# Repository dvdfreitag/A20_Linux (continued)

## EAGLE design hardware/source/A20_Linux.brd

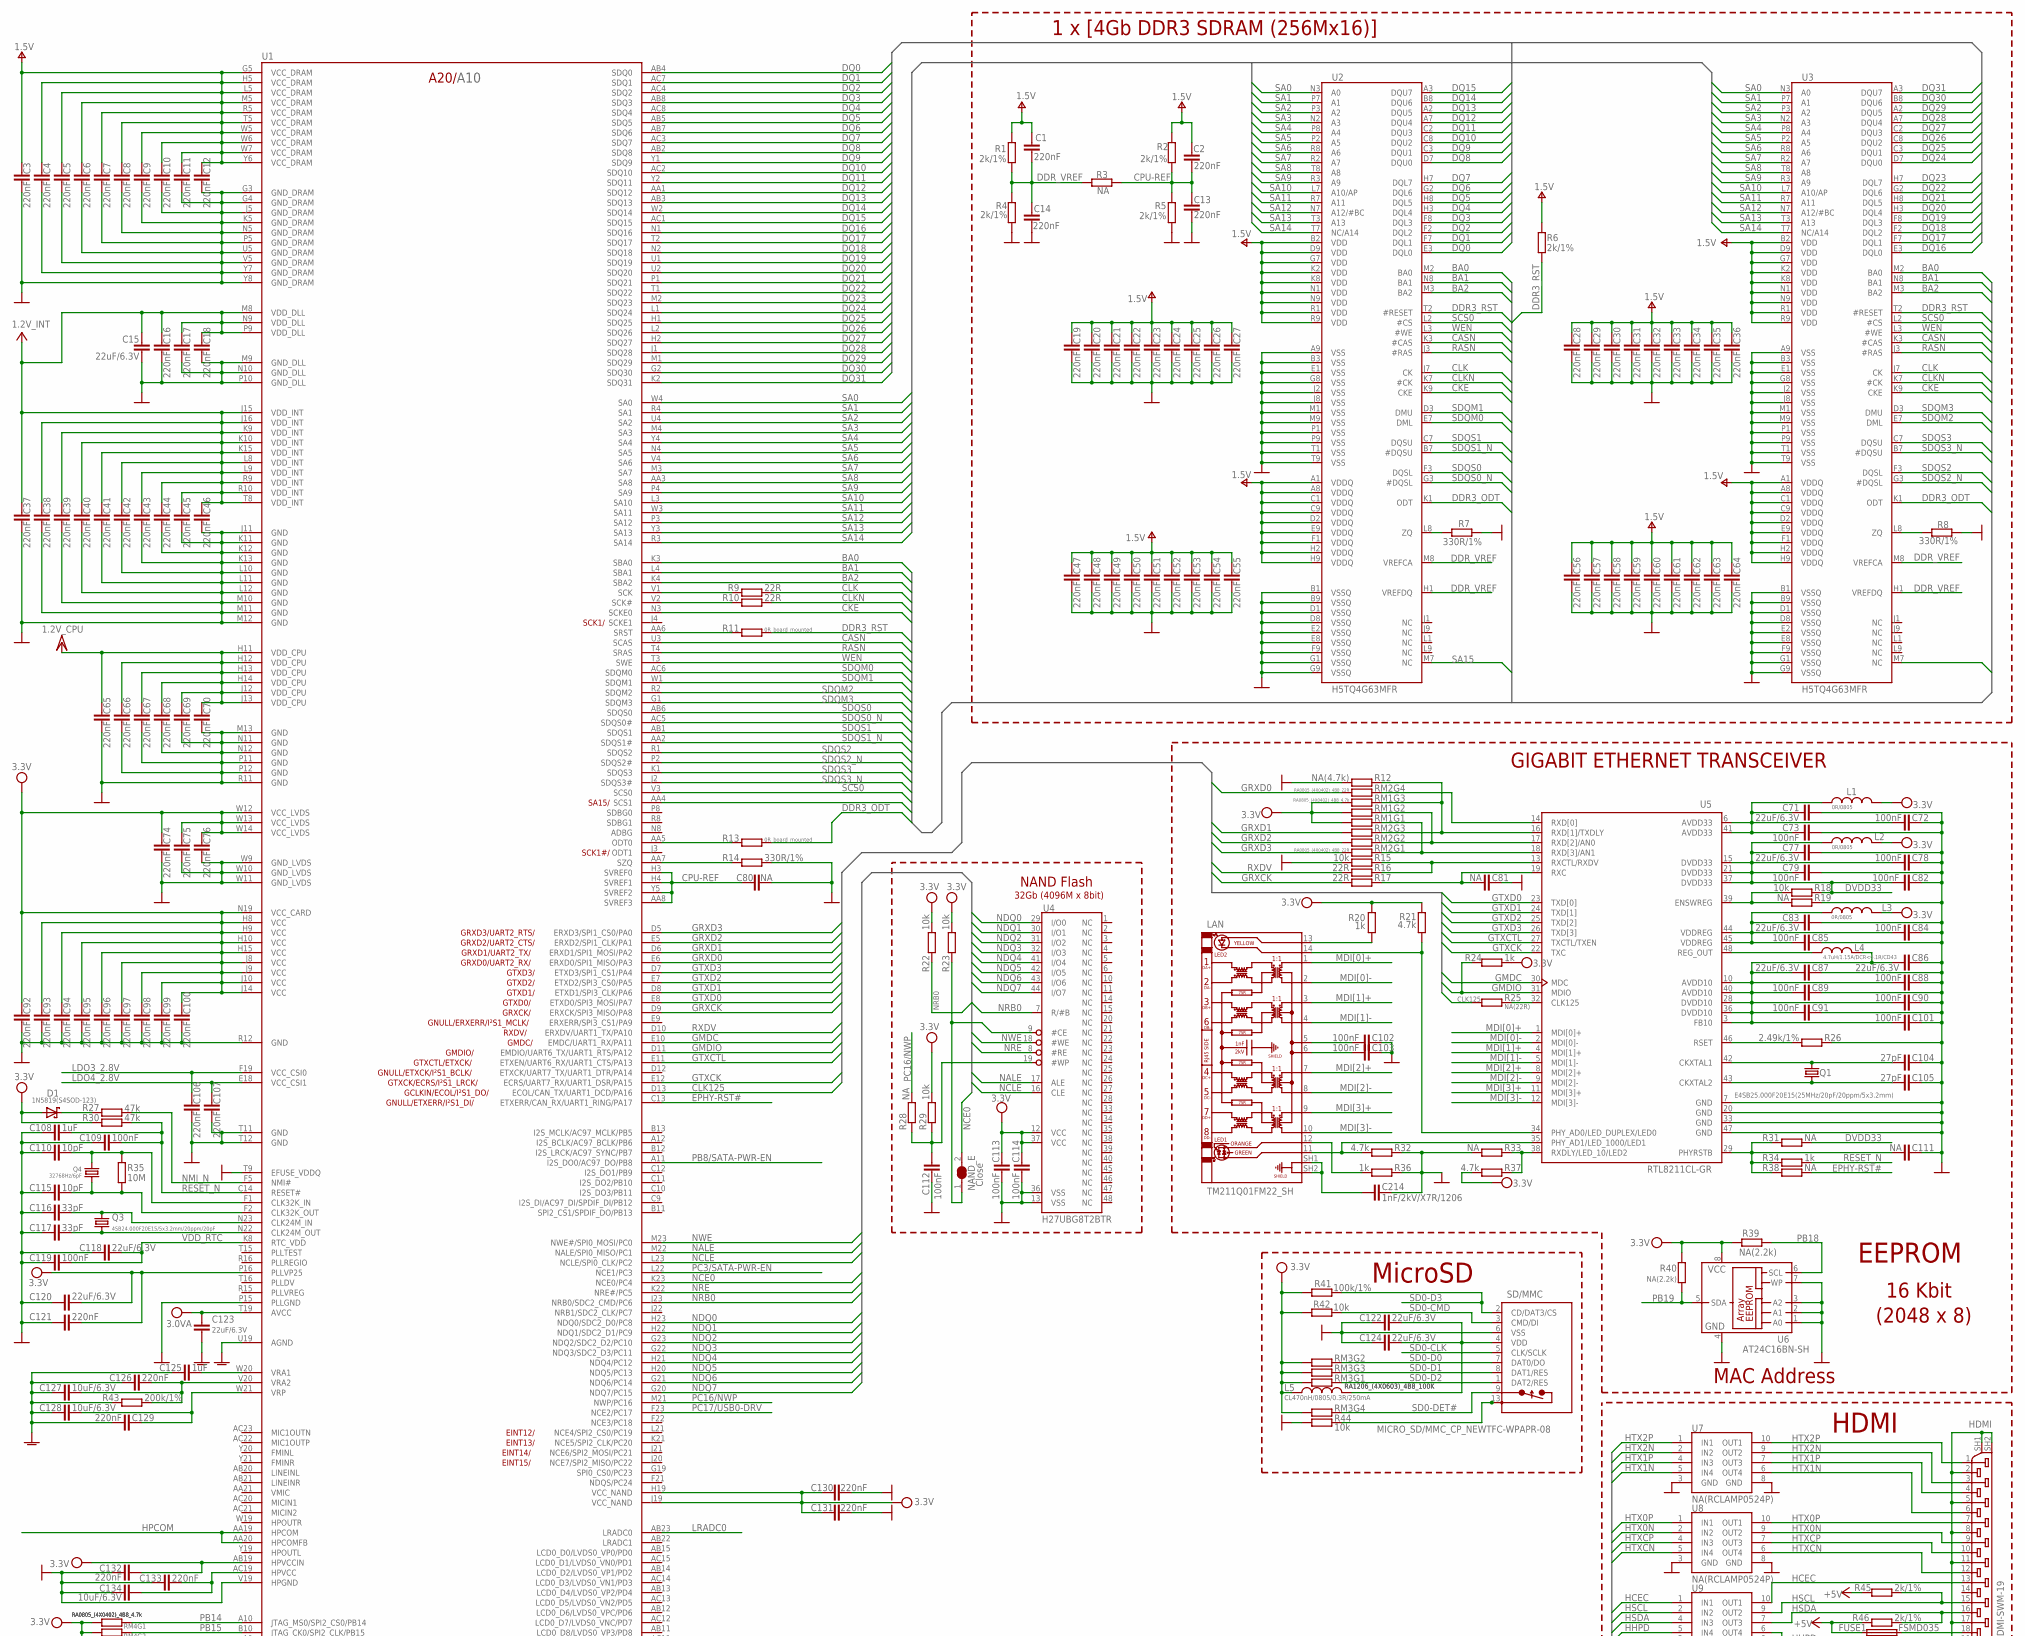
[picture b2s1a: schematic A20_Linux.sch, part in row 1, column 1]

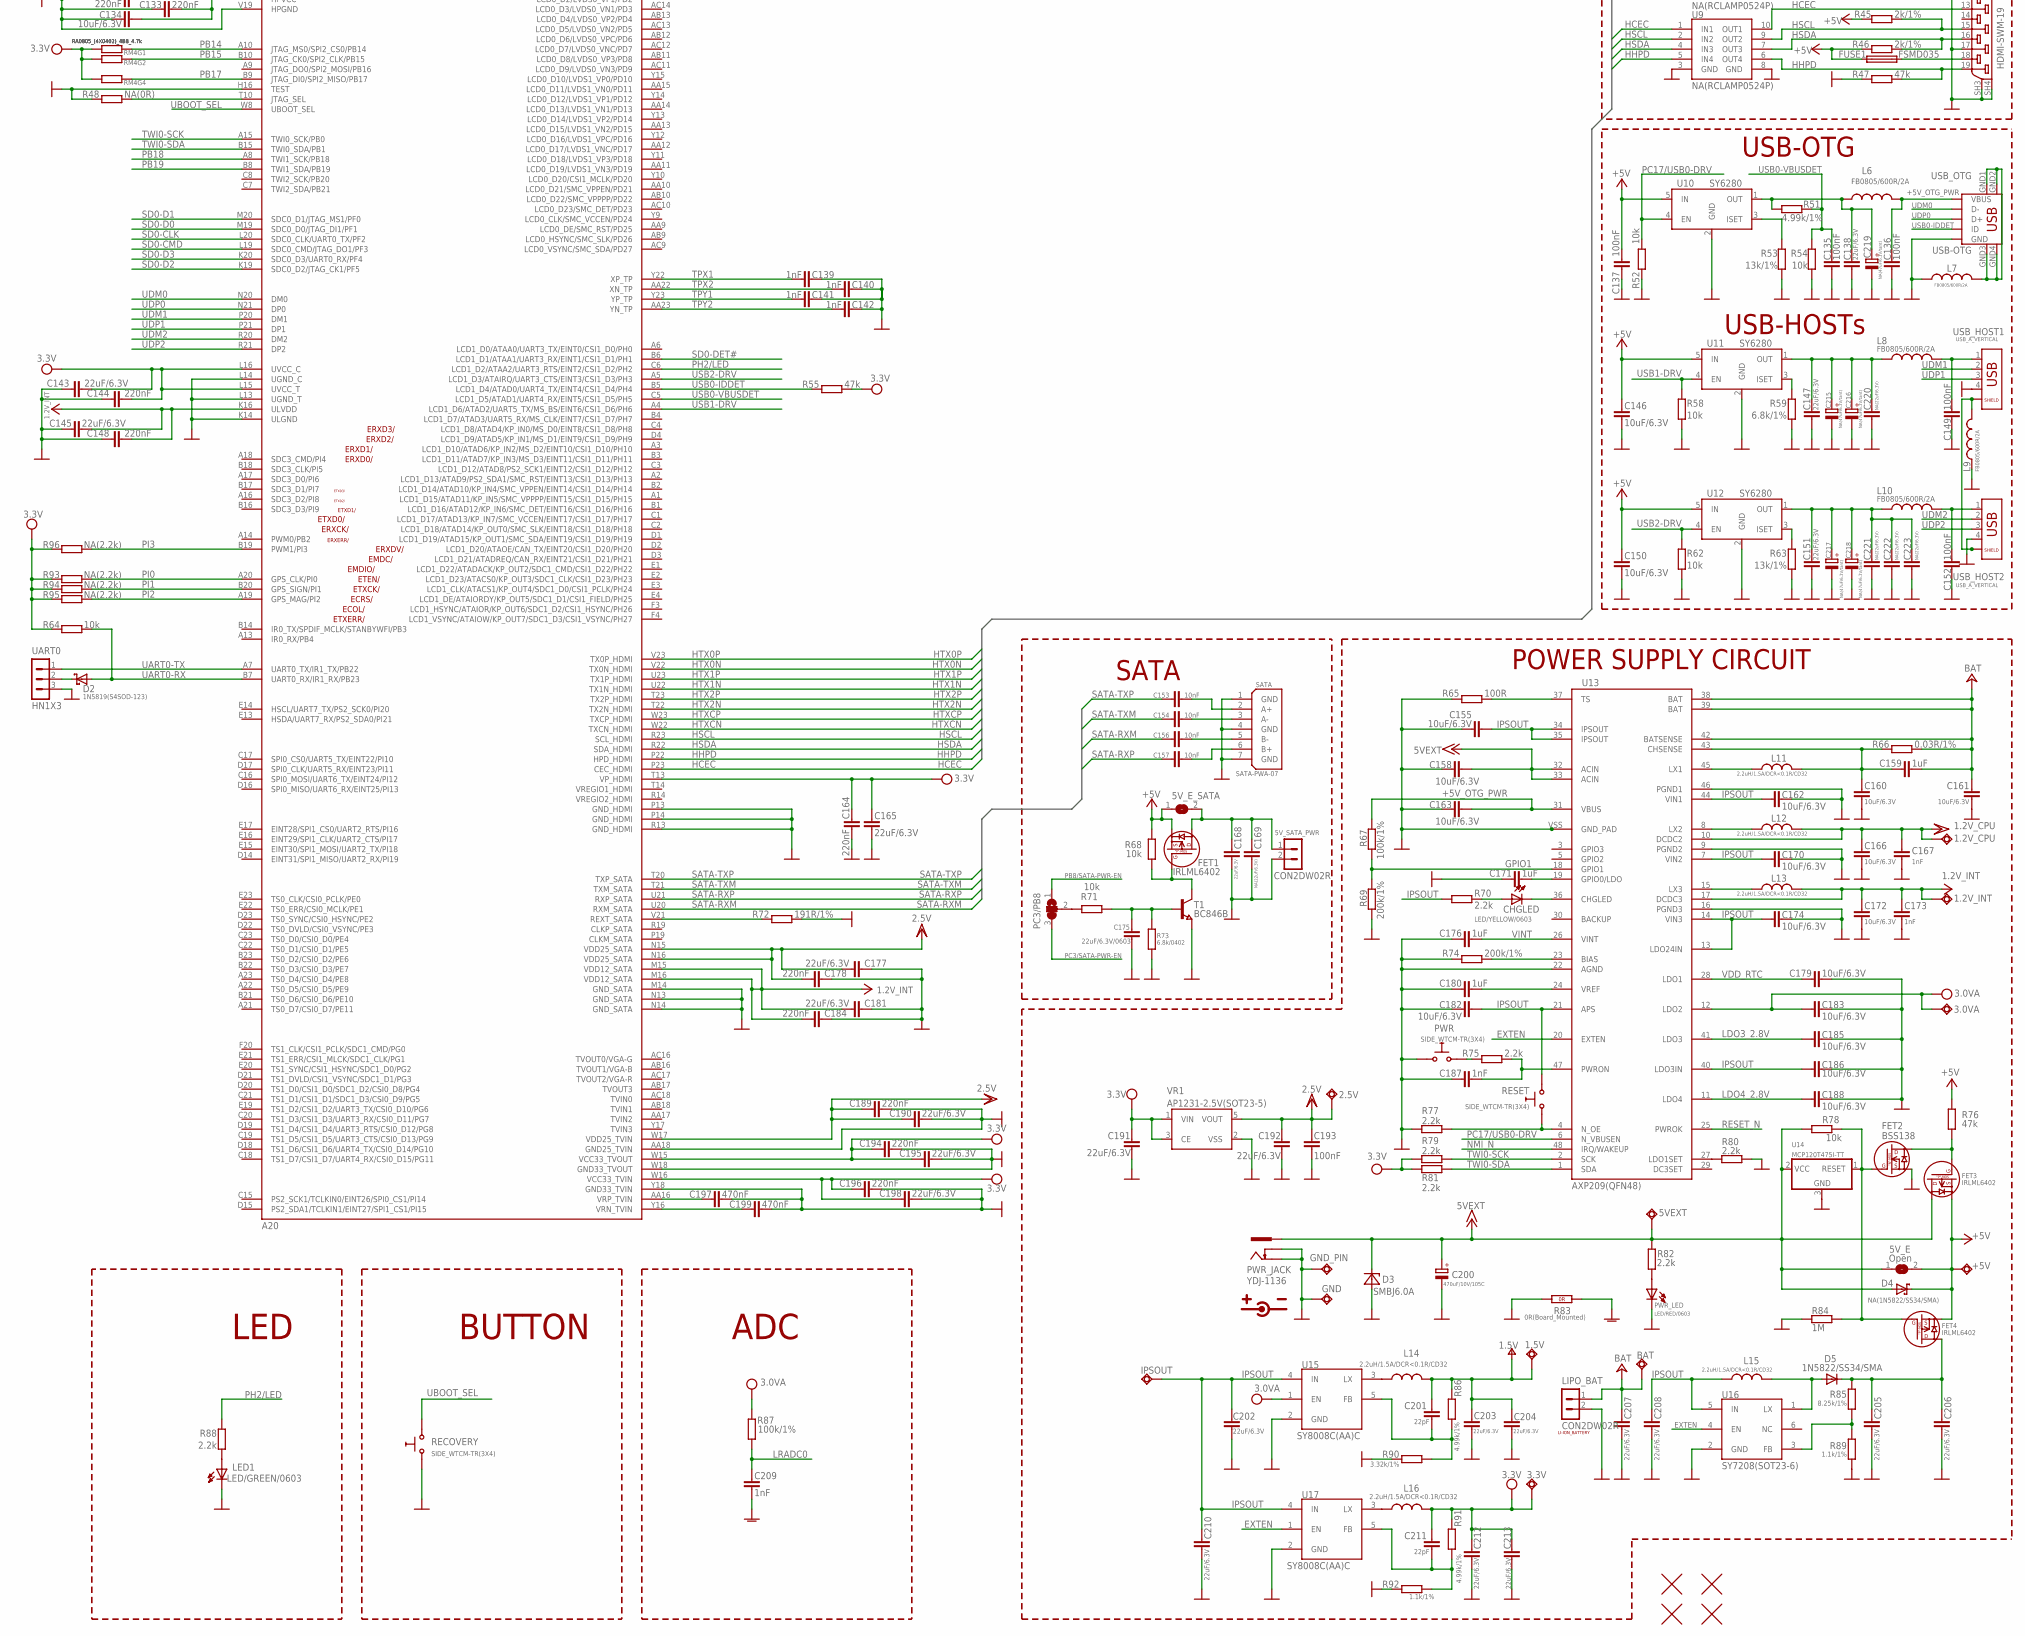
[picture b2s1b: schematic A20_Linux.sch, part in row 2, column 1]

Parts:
1.2V_CPU, 1.2V_INT, 1.5V, 2.5V, 3.0VA, 3.3V, 5VEXT: TESTPADTESTPAD_40-ROUND; TESTPAD_40-ROUND
5V_E: Open; SJ_1_SMALLER
5V_E_SATA: SJSJ_SMALLER; SJ_1_SMALLER
5V_SATA_PWR: CON2DW02R; DW02R
+5V: TESTPADTESTPAD_40-ROUND; TESTPAD_40-ROUND
BAT: TESTPADTESTPAD_40-ROUND; TESTPAD_40-ROUND
C1, C2, C3, C4, C5, C6, C7, C8, C9, C10, C11, C12, C13, C14, C16, C17, C18, C19, C20, C21, C22, C23, C24, C25, C26, C27, C28, C29, C30, C31, C32, C33, C34, C35, C36, C37, C38, C39, C40, C41, C42, C43, C44, C45, C46, C47, C48, C49, C50, C51, C52, C53, C54, C55, C56, C57, C58, C59, C60, C61, C62, C63, C64, C65, C66, C67, C68, C69, C70, C74, C75, C76, C92, C93, C94, C95, C96, C97, C98, C99, C100, C106, C107, C121, C126, C129, C130, C131, C132, C133, C144, C148, C164, C178, C184, C189, C194, C196: 220nF; C0402_TI
C15, C71, C77, C83, C86, C87, C118, C120, C122, C123, C124, C138, C143, C145, C147, C151, C165, C168, C177, C181, C190, C191, C192, C195, C198, C202, C203, C204, C205, C206, C207, C208, C210, C212, C213: 22uF/6.3V; C0603_DWS
C72, C73, C78, C79, C82, C84, C85, C88, C89, C90, C91, C101, C102, C103, C109, C112, C113, C114, C119, C135, C136, C137, C149, C152, C193: 100nF; C0402_TI
C80, C81, C111: NA; C0402_TI
C104, C105: 27pF; C0603_DWS
C108, C125, C159, C171, C176, C180: 1uF; C0603_DWS
C110, C115: 10pF; C0402_TI
C116, C117: 33pF; C0603_DWS
C127, C128, C134, C146, C150, C155, C158, C160, C161, C162, C163, C166, C170, C172, C174, C179, C182, C183, C185, C186, C188: 10uF/6.3V; C0603_DWS
C139, C140, C141, C142, C167, C173, C187, C209: 1nF; C0402_TI
C153, C154, C156, C157: 10nF; C0402_TI
C169, C220, C221, C222, C223: NA(22uF/6.3V); C0603_DWS
C175: 22uF/6.3V/0603; C0402_TI
C197, C199: 470nF; C0603_DWS
C200: 470uF/10V/105C; E2,5-6,3
C201, C211: 22pF; C0603_DWS
C214: 1nF/2kV/X7R/1206; C1206_5MILS_WS_ISO
C215, C216, C217, C218, C219: NA(47uF/6.3V/tant); CT3528_MIL
CHGLED: LED/YELLOW/0603; LED-0603
D1, D2: 1N5819(S4SOD-123); SOD-123
D3: SMBJ6.0A; DO214AA
D4: NA(1N5822/SS34/SMA); MLL-41
D5: 1N5822/SS34/SMA; MELF-MLL41
FET1, FET3, FET4: IRLML6402; SOT23
FET2: BSS138; SOT23
FUSE1: FSMD035; 1206
GND: TESTPADTESTPAD_40-ROUND; TESTPAD_40-ROUND
GND_PIN: TESTPAD3; TEST_PAD40/70/SQUARE
HDMI: HDMI-SWM-19
IPSOUT: TESTPADTESTPAD_40-ROUND; TESTPAD_40-ROUND
L1, L2, L3: 0R/0805; L0805_5MIL_DWS
L4: 4.7uH/1.15A/DCR<0.1R/CD43; CD42(43)
L5: CL470nH/0805/0.3R/250mA; L0805_5MIL_DWS
L6, L7, L8, L9, L10: FB0805/600R/2A; L0805_5MIL_DWS
L11, L12, L13, L14, L15, L16: 2.2uH/1.5A/DCR<0.1R/CD32; CD32
LAN: TM211Q01FM22_SH
LED1: LED/GREEN/0603; LED-0603
LIPO_BAT: CON2DW02R; DW02R
NAND_E: Close; SJ_1_SMALLER_CLOSE_10MILS
PC3/PB8: SJ2W5; SJ_2_SMALL_23_TIED
PWR: SIDE_WTCM-TR(3X4); SW_TAKT3X4
PWR_JACK: YDJ-1136; PWR_JACK_UNI_MILLING
PWR_LED: LED/RED/0603; LED-0603
Q1: E4SB25.000F20E15(25MHz/20pF/20ppm/5x3.2mm); HCX-4S
Q3: 4SB24.000F20E15/5x3.2mm/20ppm/20pF; HCX-4S
Q4: 32768Hz/6pF; MC-306
R1, R2, R4, R5, R6, R45, R46: 2k/1%; R0402_TI
R3, R19, R28, R31, R33, R38: NA; R0402_TI
R7, R8, R14: 330R/1%; R0603_5MIL_DWS
R9, R10, R16, R17: 22R; R0402_TI
R11, R13: 0R_board_mounted; R0402_TI_0R
R12: NA(4.7k); R0402_TI
R15, R18, R22, R23, R29, R42, R44, R52, R54, R58, R62, R64, R68, R71, R78: 10k; R0402_TI
R20, R24, R34, R36: 1k; R0402_TI
R21, R32, R37: 4.7k; R0402_TI
R25: NA(22R); R0402_TI
R26: 2.49k/1%; R0603_5MIL_DWS
R27, R30, R47, R55, R76: 47k; R0402_TI
R35: 10M; R0402_TI
R39, R40, R93, R94, R95, R96: NA(2.2k); R0402_TI
R41, R67, R87: 100k/1%; R0603_5MIL_DWS
R43, R69, R74: 200k/1%; R0603_5MIL_DWS
R48: NA(0R); R0603_5MIL_DWS
R51, R86, R91: 4.99k/1%; R0603_5MIL_DWS
R53, R63: 13k/1%; R0603_5MIL_DWS
R59: 6.8k/1%; R0603_5MIL_DWS
R65: 100R; R0603_5MIL_DWS
R66: 0.03R/1%; R1206_5MIL_WS
R70, R75, R77, R79, R80, R81, R82, R88: 2.2k; R0402_TI
R72: 191R/1%; R0603_5MIL_DWS
R73: 6.8k/0402; R0603_5MIL_DWS
R83: 0R(Board_Mounted); 0603_0R
R84: 1M; R0402_TI
R85: 8.25k/1%; R0603_5MIL_DWS
R89, R92: 1.1k/1%; R0603_5MIL_DWS
R90: 3.32k/1%; R0603_5MIL_DWS
RECOVERY: SIDE_WTCM-TR(3X4); SW_TAKT3X4
RESET: SIDE_WTCM-TR(3X4); SW_TAKT3X4
RM1, RM4: RA0805_(4X0402)_4B8_4.7k; R_MATRIX_4_0402_25X625
RM2: RA0805_(4X0402)_4B8_22R; R_MATRIX_4_0402_25X625
RM3: RA1206_(4X0603)_4B8_100K; R_MATRIX_4
SATA: SATA-PWA-07
SD/MMC: MICRO_SD/MMC_CP_NEWTFC-WPAPR-08; TFC-WPAPR-08
T1: BC846B; SOT23
U1: A20; TFBGA441
U2, U3: H5TQ4G63MFR; FBGA96_SK
U4: H27UBG8T2BTR; TSOP48
U5: RTL8211CL-GR; LQFP48
U6: AT24C16BN-SH; SO-08MN
U7, U8, U9: NA(RCLAMP0524P); SLP2510P8
U10, U11, U12: SY6280; SOT23-5
U13: AXP209(QFN48); QFN48
U14: MCP120T475I-TT; SOT23
U15, U17: SY8008C(AA)C; SOT23-5
U16: SY7208(SOT23-6); SOT23-6
U18, U19, U20, U21: FIDUCIAL; FIDUCIAL-1X3
UART0: HN1X3
USB_HOST1, USB_HOST2: USB_A_VERTICAL; USB_A_VERTICAL_PTH
USB_OTG: USB-OTG; USB_MINI_9PIN
VR1: AP1231-2.5V(SOT23-5); SOT-23-5

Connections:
5VEXT: 5VEXT.1, 5V_E.1, C158.2, C200.+, D3.C, D4.A, FET3.3 (D), PWR_JACK.+, R78.1, R82.1, U13.32 (ACIN), U13.33 (ACIN), U14.2 (VCC)
+5V: 5V_E.2, 5V_E_SATA.1, +5V.1, C137.1, C146.1, C150.1, D4.K (C), FET1.2 (S), FET3.2 (S), FET4.2 (S), FUSE1.1, R45.2, R46.2, R68.1, R76.2, U10.5 (IN), U11.5 (IN), U12.5 (IN)
+5V_OTG_PWR: C136.1, C163.2, L6.1, R67.1, U13.31 (VBUS), USB_OTG.VBUS
+24V: BAT.1, C159.2, C161.1, C207.2, LIPO_BAT.1, R66.2, U13.38 (BAT), U13.39 (BAT), U13.42 (BATSENSE)
AVDD1: C71.2, C72.2, C73.2, L1.2, U5.6 (AVDD33), U5.41 (AVDD33)
AVDD/DVDD(1.05V): C86.2, C87.2, C88.2, C89.2, C90.2, C91.2, C101.2, L4.2, U5.3 (FB10), U5.10 (AVDD10), U5.28 (DVDD10), U5.36 (DVDD10), U5.40 (AVDD10)
BA0: U1.K3 (SBA0), U2.M2 (BA0), U3.M2 (BA0)
BA1: U1.L4 (SBA1), U2.N8 (BA1), U3.N8 (BA1)
BA2: U1.K4 (SBA2), U2.M3 (BA2), U3.M3 (BA2)
CASN: U1.U3 (SCAS), U2.K3 (#CAS), U3.K3 (#CAS)
CKE: U1.N3 (SCKE0), U2.K9 (CKE), U3.K9 (CKE)
CLK: R9.1, U2.J7 (CK), U3.J7 (CK)
CLK125: R25.1, U1.D13 (ECOL/CAN_TX/UART1_DCD/PA16)
CLKN: R10.1, U2.K7 (#CK), U3.K7 (#CK)
CPU-REF: C2.2, C13.2, C80.2, R2.1, R3.2, R5.2, U1.AA8 (SVREF3), U1.H3 (SVREF0), U1.H4 (SVREF1), U1.Y5 (SVREF2)
DDR3_ODT: R13.1, U2.K1 (ODT), U3.K1 (ODT)
DDR3_RST: R6.1, R11.1, U2.T2 (#RESET), U3.T2 (#RESET)
DDR_VREF: C1.2, C14.2, R1.1, R3.1, R4.2, U2.H1 (VREFDQ), U2.M8 (VREFCA), U3.H1 (VREFDQ), U3.M8 (VREFCA)
DQ0: U1.AB4 (SDQ0), U2.E3 (DQL0)
DQ1: U1.AC7 (SDQ1), U2.F7 (DQL1)
DQ2: U1.AC4 (SDQ2), U2.F2 (DQL2)
DQ3: U1.AB8 (SDQ3), U2.F8 (DQL3)
DQ4: U1.AC8 (SDQ4), U2.H3 (DQL4)
DQ5: U1.AB5 (SDQ5), U2.H8 (DQL5)
DQ6: U1.AB7 (SDQ6), U2.G2 (DQL6)
DQ7: U1.AC3 (SDQ7), U2.H7 (DQL7)
DQ8: U1.AB2 (SDQ8), U2.D7 (DQU0)
DQ9: U1.Y1 (SDQ9), U2.C3 (DQU1)
DQ10: U1.AC2 (SDQ10), U2.C8 (DQU2)
DQ11: U1.Y2 (SDQ11), U2.C2 (DQU3)
DQ12: U1.AA1 (SDQ12), U2.A7 (DQU4)
DQ13: U1.AB3 (SDQ13), U2.A2 (DQU5)
DQ14: U1.W2 (SDQ14), U2.B8 (DQU6)
DQ15: U1.AC1 (SDQ15), U2.A3 (DQU7)
DQ16: U1.N1 (SDQ16), U3.E3 (DQL0)
DQ17: U1.T2 (SDQ17), U3.F7 (DQL1)
DQ18: U1.N2 (SDQ18), U3.F2 (DQL2)
DQ19: U1.U1 (SDQ19), U3.F8 (DQL3)
DQ20: U1.U2 (SDQ20), U3.H3 (DQL4)
DQ21: U1.P1 (SDQ21), U3.H8 (DQL5)
DQ22: U1.T1 (SDQ22), U3.G2 (DQL6)
DQ23: U1.M2 (SDQ23), U3.H7 (DQL7)
DQ24: U1.L1 (SDQ24), U3.D7 (DQU0)
DQ25: U1.H1 (SDQ25), U3.C3 (DQU1)
DQ26: U1.L2 (SDQ26), U3.C8 (DQU2)
DQ27: U1.H2 (SDQ27), U3.C2 (DQU3)
DQ28: U1.J1 (SDQ28), U3.A7 (DQU4)
DQ29: U1.M1 (SDQ29), U3.A2 (DQU5)
DQ30: U1.G2 (SDQ30), U3.B8 (DQU6)
DQ31: U1.K2 (SDQ31), U3.A3 (DQU7)
DVDD33: C77.2, C78.2, C79.2, C82.2, L2.2, R18.1, R31.1, U5.15 (DVDD33), U5.21 (DVDD33), U5.37 (DVDD33)
EPHY-RST#: R38.1, U1.C13 (ETXERR/CAN_RX/UART1_RING/PA17)
EXTEN: U13.20 (EXTEN), U16.4 (EN), U17.1 (EN)
GMDC: U1.E10 (EMDC/UART1_RX/PA11), U5.30 (MDC)
GMDIO: R24.1, U1.D11 (EMDIO/UART6_TX/UART1_RTS/PA12), U5.31 (MDIO)
GND: 5V_SATA_PWR.2, C3.1, C4.1, C5.1, C6.1, C7.1, C8.1, C9.1, C10.1, C11.1, C12.1, C13.1, C14.1, C15.1, C16.1, C17.1, C18.1, C19.1, C20.1, C21.1, C22.1, C23.1, C24.1, C25.1, C26.1, C27.1, C28.1, C29.1, C30.1, C31.1, C32.1, C33.1, C34.1, C35.1, C36.1, C37.1, C38.1, C39.1, C40.1, C41.1, C42.1, C43.1, C44.1, C45.1, C46.1, C47.1, C48.1, C49.1, C50.1, C51.1, C52.1, C53.1, C54.1, C55.1, C56.1, C57.1, C58.1, C59.1, C60.1, C61.1, C62.1, C63.1, C64.1, C65.1, C66.1, C67.1, C68.1, C69.1, C70.1, C71.1, C72.1, C73.1, C74.1, C75.1, C76.1, C77.1, C78.1, C79.1, C80.1, C81.2, C82.1, C83.1, C84.1, C85.1, C86.1, C87.1, C88.1, C89.1, C90.1, C91.1, C92.1, C93.1, C94.1, C95.1, C96.1, C97.1, C98.1, C99.1, C100.1, C101.1, C102.1, C103.1, C104.1, C105.1, C106.1, C107.1, C108.1, C109.1, C110.1, C111.1, C112.1, C113.1, C114.1, C115.1, C116.1, C117.1, C118.1, C119.1, C120.1, C121.1, C122.1, C124.1, C130.1, C131.1, C132.1, C133.1, C134.1, C135.2, C136.2, C137.2, C138.1, C139.1, C140.1, C141.1, C142.1, C143.1, C144.1, C145.1, C146.2, C147.1, C148.1, C149.2, C150.2, C151.1, C152.2, C155.1, C158.1, C160.2, C161.2, C162.2, C163.1, C164.2, C165.1, C166.2, C167.2, C168.1, C169.1, C170.2, C171.1, C172.2, C173.2, C174.2, C175.2, C176.1, C177.1, C178.1, C179.2, C180.1, C181.1, C182.1, C183.2, C184.1, C185.2, C186.2, C187.1, C188.2, C189.2, C190.1, C191.2, C192.2, C193.2, C194.2, C195.1, C196.2, C197.1, C198.1, C199.1, C200.-, C202.2, C203.2, C204.2, C205.2, C206.2, C207.1, C208.1, C210.2, C212.2, C213.2, C214.1, C215.-, C216.-, C217.-, C218.-, C219.-, C220.1, C221.1, C222.1, C223.1, D3.A, FET2.2 (S), GND.1, GND_PIN.P$1, HDMI.2, HDMI.5, HDMI.8, HDMI.11, HDMI.17, HDMI.SH1 (20), HDMI.SH2 (21), HDMI.SH3 (22), HDMI.SH4 (23), L7.1, L9.1, LED1.C, LIPO_BAT.2, PWR.2_1 (0), PWR_JACK.-, PWR_JACK.--, PWR_LED.C, R4.1, R5.1, R7.1, R8.1, R12.2, R14.1, R15.2, R19.1, R26.1, R32.1, R33.2, R36.1, R44.2, R47.2, R48.2, R52.1, R53.1, R54.1, R58.1, R59.1, R62.1, R63.1, R65.1, R69.2, R72.1, R73.1, R74.1, R77.1, R80.2, R83.1 (1.1), R84.1, R89.2, R90.2, R92.2, RECOVERY.1_1 (1), SATA.1 (GND), SATA.4 (GND), SATA.7 (GND), SD/MMC.6 (VSS), T1.2 (E), U1.AA18 (GND25_TVIN), U1.G3 (GND_DRAM), U1.G4 (GND_DRAM), U1.H16 (TEST), U1.J5 (GND_DRAM), U1.J11 (GND), U1.K5 (GND_DRAM), U1.K11 (GND), U1.K12 (GND), U1.K13 (GND), U1.K14 (ULGND), U1.L10 (GND), U1.L11 (GND), U1.L12 (GND), U1.L13 (UGND_T), U1.L14 (UGND_C), U1.M9 (GND_DLL), U1.M10 (GND), U1.M11 (GND), U1.M12 (GND), U1.M13 (GND), U1.M14 (GND_SATA), U1.N5 (GND_DRAM), U1.N10 (GND_DLL), U1.N11 (GND), U1.N12 (GND), U1.N13 (GND_SATA), U1.N14 (GND_SATA), U1.P5 (GND_DRAM)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
GNDA: C123.1, C125.1, C126.1, C127.1, C128.1, C129.1, C209.2, R43.2, R83.2 (1.2), U1.U19 (AGND)
GPIO1: R67.2, R69.1, U13.18 (GPIO1)
GRXCK: R17.2, U1.D9 (ERXCK/SPI3_MISO/PA8)
GRXD0: RM2.4.2 (2), U1.E6 (ERXD0/SPI1_MISO/PA3)
GRXD1: RM2.3.2 (2), U1.D6 (ERXD1/SPI1_MOSI/PA2)
GRXD2: RM2.2.2 (2), U1.E5 (ERXD2/SPI1_CLK/PA1)
GRXD3: RM2.1.2 (2), U1.D5 (ERXD3/SPI1_CS0/PA0)
GTXCK: U1.E12 (ECRS/UART7_RX/UART1_DSR/PA15), U5.22 (TXC)
GTXCTL: U1.E11 (ETXEN/UART6_RX/UART1_CTS/PA13), U5.27 (TXCTL/TXEN)
GTXD0: U1.E8 (ETXD0/SPI3_MOSI/PA7), U5.23 (TXD[0])
GTXD1: U1.D8 (ETXD1/SPI3_CLK/PA6), U5.24 (TXD[1])
GTXD2: U1.E7 (ETXD2/SPI3_CS0/PA5), U5.25 (TXD[2])
GTXD3: U1.D7 (ETXD3/SPI1_CS1/PA4), U5.26 (TXD[3])
HCEC: HDMI.13, U1.P23 (CEC_HDMI), U9.1 (IN1), U9.10 (OUT1)
HDMI_5V_SOURCE: FUSE1.2, HDMI.18
HHPD: HDMI.19, R47.1, U1.P22 (HPD_HDMI), U9.5 (IN4), U9.6 (OUT4)
HPCOM: U1.AA19 (HPCOM), U1.AA20 (HPCOMFB)
HSCL: HDMI.15, R45.1, U1.R23 (SCL_HDMI), U9.2 (IN2), U9.9 (OUT2)
HSDA: HDMI.16, R46.1, U1.R22 (SDA_HDMI), U9.4 (IN3), U9.7 (OUT3)
HTX0N: HDMI.9, U1.V22 (TX0N_HDMI), U8.2 (IN2), U8.9 (OUT2)
HTX0P: HDMI.7, U1.V23 (TX0P_HDMI), U8.1 (IN1), U8.10 (OUT1)
HTX1N: HDMI.6, U1.U22 (TX1N_HDMI), U7.5 (IN4), U7.6 (OUT4)
HTX1P: HDMI.4, U1.U23 (TX1P_HDMI), U7.4 (IN3), U7.7 (OUT3)
HTX2N: HDMI.3, U1.T22 (TX2N_HDMI), U7.2 (IN2), U7.9 (OUT2)
HTX2P: HDMI.1, U1.T23 (TX2P_HDMI), U7.1 (IN1), U7.10 (OUT1)
HTXCN: HDMI.12, U1.W22 (TXCN_HDMI), U8.5 (IN4), U8.6 (OUT4)
HTXCP: HDMI.10, U1.W23 (TXCP_HDMI), U8.4 (IN3), U8.7 (OUT3)
IPSOUT: C155.2, C162.1, C170.1, C174.1, C182.2, C186.1, C202.1, C208.2, C210.1, IPSOUT.1, L15.1, R70.1, RESET.1_1 (1), U13.7 (VIN2), U13.13 (LDO24IN), U13.14 (VIN3), U13.21 (APS), U13.34 (IPSOUT), U13.35 (IPSOUT), U13.40 (LDO3IN), U13.44 (VIN1), U15.4 (IN), U16.5 (IN), U17.4 (IN)
LAN_SH: C214.2, LAN.SH1, LAN.SH2
LDO3_2.8V: C106.2, C185.1, U1.F19 (VCC_CSI0), U13.41 (LDO3)
LDO4_2.8V: C107.2, C188.1, U1.E18 (VCC_CSI1), U13.11 (LDO4)
LRADC0: C209.1, R87.2, U1.AB23 (LRADC0)
MDI[0]+: LAN.1, U5.1 (MDI[0]+)
MDI[0]-: LAN.2, U5.2 (MDI[0]-)
MDI[1]+: LAN.3, U5.4 (MDI[1]+)
MDI[1]-: LAN.4, U5.5 (MDI[1]-)
MDI[2]+: LAN.7, U5.8 (MDI[2]+)
MDI[2]-: LAN.8, U5.9 (MDI[2]-)
MDI[3]+: LAN.9, U5.11 (MDI[3]+)
MDI[3]-: LAN.10, U5.12 (MDI[3]-)
unnamed: C133.2, C134.2, U1.AC19 (HPVCC)
unnamed: R14.2, U1.AA7 (SZQ)
unnamed: R7.2, U2.L8 (ZQ)
unnamed: CHGLED.A, R70.2
unnamed: PC3/PB8.2, R71.2
unnamed: D2.C, UART0.2
unnamed: L14.1, U15.3 (LX)
unnamed: C171.2, U13.19 (GPIO0/LDO)
unnamed: D1.C, R27.2
unnamed: CHGLED.C, U13.36 (CHGLED)
unnamed: R80.1, U13.27 (LDO1SET)
unnamed: C151.2, C217.+, C218.+, C221.2, C222.2, C223.2, L10.1, U12.1 (OUT)
unnamed: C110.2, Q4.1, R35.1, U1.F1 (CLK32K_IN)
unnamed: R8.2, U3.L8 (ZQ)
unnamed: L4.1, U5.48 (REG_OUT)
unnamed: C175.1, R71.1, R73.2, T1.1 (B)
unnamed: FET1.1 (G), R68.2, T1.3 (C)
unnamed: C201.2, R86.2, R90.1, U15.5 (FB)
unnamed: R26.2, U5.46 (RSET)
unnamed: FET2.3 (D), FET3.1 (G), R76.1
unnamed: C104.2, Q1.2, U5.42 (CKXTAL1)
unnamed: C205.1, C206.1, D5.1 (C), FET4.3 (D), R85.2
unnamed: 5V_E_SATA.2, 5V_SATA_PWR.1, C168.2, C169.2, FET1.3 (D)
unnamed: C105.2, Q1.1, U5.43 (CKXTAL2)
unnamed: C111.2, R31.2, R34.2, R38.2, U5.29 (PHYRSTB)
unnamed: C102.2, LAN.5
unnamed: C103.2, LAN.6
unnamed: R33.1, R37.1, U5.38 (RXDLY/LED_10/LED2)
unnamed: LAN.12, R36.2
unnamed: LAN.11, R32.2, U5.35 (PHY_AD1/LED_1000/LED1)
unnamed: FET2.1 (G), FET4.1 (G), R78.2, R84.2, U14.1 (RESET)
unnamed: R18.2, R19.2, U5.39 (ENSWREG)
unnamed: LAN.13, R20.2
unnamed: C81.1, R17.1, U5.19 (RXC)
unnamed: R15.1, R16.1, U5.13 (RXCTL/RXDV)
unnamed: PWR.1_1 (1), R75.1
unnamed: C197.2, U1.AA16 (VRP_TVIN)
unnamed: RM2.4.1 (1), U5.14 (RXD[0])
unnamed: R12.1, RM1.3.1 (1), RM2.3.1 (1), U5.16 (RXD[1]/TXDLY)
unnamed: RM1.2.1 (1), RM2.2.1 (1), U5.17 (RXD[2]/AN0)
unnamed: RM1.1.1 (1), RM2.1.1 (1), U5.18 (RXD[3]/AN1)
unnamed: LAN.14, R21.1, U5.34 (PHY_AD0/LED_DUPLEX/LED0)
unnamed: R25.2, U5.32 (CLK125)
unnamed: R44.1, SD/MMC.10 (PACK1), SD/MMC.11 (PACK2), SD/MMC.12 (PACK3), SD/MMC.13 (PACK4)
unnamed: L16.1, U17.3 (LX)
unnamed: C211.2, R91.2, R92.1, U17.5 (FB)
unnamed: R53.2, U10.3 (ISET)
unnamed: C138.2, C219.+, L6.2, R51.2, U10.1 (OUT)
unnamed: R63.2, U12.3 (ISET)
unnamed: C153.2, SATA.2 (A+)
unnamed: C152.1, L10.2, USB_HOST2.1
unnamed: C154.2, SATA.3 (A-)
unnamed: C156.2, SATA.5 (B-)
unnamed: C157.2, SATA.6 (B+)
unnamed: C115.2, Q4.4 (2), R35.2, U1.F2 (CLK32K_OUT)
unnamed: R72.2, U1.V21 (REXT_SATA)
unnamed: R74.2, U13.23 (BIAS)
unnamed: C128.2, C129.2, U1.W21 (VRP)
unnamed: D5.2 (A), L15.2, U16.1 (LX)
unnamed: C112.2, R28.2, R29.2, U4.19 (#WP)
unnamed: R65.2, U13.37 (TS)
unnamed: R85.1, R89.1, U16.3 (FB)
unnamed: L11.1, U13.45 (LX1)
unnamed: C159.1, C160.1, L11.2, R66.1, U13.43 (CHSENSE)
unnamed: PWR_LED.A, R82.2
unnamed: L12.1, U13.8 (LX2)
unnamed: L13.1, U13.15 (LX3)
unnamed: C180.2, U13.24 (VREF)
unnamed: C125.2, U1.W20 (VRA1)
unnamed: R59.2, U11.3 (ISET)
unnamed: C187.2, R75.2, U13.47 (PWRON)
unnamed: R77.2, RESET.2_1 (0), U13.4 (N_OE)
unnamed: C126.2, C127.2, R43.1, U1.V20 (VRA2)
unnamed: R48.1, U1.T10 (JTAG_SEL)
unnamed: L9.2, USB_HOST1.P$3 (5), USB_HOST1.P$4 (6), USB_HOST2.P$3 (5), USB_HOST2.P$4 (6)
unnamed: C149.1, L8.2, USB_HOST1.1
unnamed: C147.2, C215.+, C216.+, C220.2, L8.1, U11.1 (OUT)
unnamed: C199.2, U1.Y16 (VRN_TVIN)
unnamed: LED1.A, R88.2
unnamed: NAND_E.1, R23.2, U4.9 (#CE)
unnamed: L7.2, USB_OTG.GND1, USB_OTG.GND2, USB_OTG.GND3, USB_OTG.GND4
NALE: U1.M22 (NALE/SPI0_MISO/PC1), U4.17 (ALE)
NCE0: NAND_E.2, U1.K23 (NCE0/PC4)
NCLE: U1.L23 (NCLE/SPI0_CLK/PC2), U4.16 (CLE)
NDQ0: U1.H23 (NDQ0/SDC2_D0/PC8), U4.29 (I/O0)
NDQ1: U1.H22 (NDQ1/SDC2_D1/PC9), U4.30 (I/O1)
NDQ2: U1.G23 (NDQ2/SDC2_D2/PC10), U4.31 (I/O2)
NDQ3: U1.G22 (NDQ3/SDC2_D3/PC11), U4.32 (I/O3)
NDQ4: U1.H21 (NDQ4/PC12), U4.41 (I/O4)
NDQ5: U1.H20 (NDQ5/PC13), U4.42 (I/O5)
NDQ6: U1.G21 (NDQ6/PC14), U4.43 (I/O6)
NDQ7: U1.G20 (NDQ7/PC15), U4.44 (I/O7)
NMI_N: R27.1, U1.F5 (NMI#), U13.48 (IRQ/WAKEUP)
NRB0: R22.2, U1.J23 (NRB0/SDC2_CMD/PC6), U4.7 (R/#B)
NRE: U1.K22 (NRE#/PC5), U4.8 (#RE)
NWE: U1.M23 (NWE#/SPI0_MOSI/PC0), U4.18 (#WE)
ODT0: R13.2, U1.AA5 (ODT0)
PB8/SATA-PWR-EN: PC3/PB8.1, U1.A11 (I2S_DO0/AC97_DO/PB8)
PB14: RM4.1.1 (1), U1.A10 (JTAG_MS0/SPI2_CS0/PB14)
PB15: RM4.2.1 (1), U1.B10 (JTAG_CK0/SPI2_CLK/PB15)
PB17: RM4.4.1 (1), U1.B9 (JTAG_DI0/SPI2_MISO/PB17)
PB18: R39.2, U1.A8 (TWI1_SCK/PB18), U6.6 (SCL)
PB19: R40.1, U1.B8 (TWI1_SDA/PB19), U6.5 (SDA)
PC3/SATA-PWR-EN: PC3/PB8.3, U1.L22 (NCE1/PC3)
PC16/NWP: R28.1, U1.M21 (NWP/PC16)
PC17/USB0-DRV: R52.2, U1.F23 (NCE2/PC17), U10.4 (EN), U13.6 (N_VBUSEN)
PH2/LED: R88.1, U1.C6 (LCD1_D2/ATAA2/UART3_RTS/EINT2/CSI1_D2/P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)
PI0: R93.1, U1.A20 (GPS_CLK/PI0)
PI1: R94.1, U1.B20 (GPS_SIGN/PI1)
PI2: R95.1, U1.A19 (GPS_MAG/PI2)
PI3: R96.1, U1.B19 (PWM1/PI3)
RASN: U1.T4 (SRAS), U2.J3 (#RAS), U3.J3 (#RAS)
RESET_N: C108.2, C109.2, R30.1, R34.1, U1.C14 (RESET#), U13.25 (PWROK)
RXDV: R16.2, U1.D10 (ERXDV/UART1_TX/PA10)
SA0: U1.W4 (SA0), U2.N3 (A0), U3.N3 (A0)
SA1: U1.R4 (SA1), U2.P7 (A1), U3.P7 (A1)
SA2: U1.U4 (SA2), U2.P3 (A2), U3.P3 (A2)
SA3: U1.M4 (SA3), U2.N2 (A3), U3.N2 (A3)
SA4: U1.Y4 (SA4), U2.P8 (A4), U3.P8 (A4)
SA5: U1.N4 (SA5), U2.P2 (A5), U3.P2 (A5)
SA6: U1.V4 (SA6), U2.R8 (A6), U3.R8 (A6)
SA7: U1.M3 (SA7), U2.R2 (A7), U3.R2 (A7)
SA8: U1.AA3 (SA8), U2.T8 (A8), U3.T8 (A8)
SA9: U1.P4 (SA9), U2.R3 (A9), U3.R3 (A9)
SA10: U1.L3 (SA10), U2.L7 (A10/AP), U3.L7 (A10/AP)
SA11: U1.W3 (SA11), U2.R7 (A11), U3.R7 (A11)
SA12: U1.P3 (SA12), U2.N7 (A12/#BC), U3.N7 (A12/#BC)
SA13: U1.Y3 (SA13), U2.T3 (A13), U3.T3 (A13)
SA14: U1.R3 (SA14), U2.T7 (NC/A14), U3.T7 (NC/A14)
SA15: U1.AA4 (SCS1), U2.M7 (NC), U3.M7 (NC)
SATA-RXM: C156.1, U1.U20 (RXM_SATA)
SATA-RXP: C157.1, U1.U21 (RXP_SATA)
SATA-TXM: C154.1, U1.T21 (TXM_SATA)
SATA-TXP: C153.1, U1.T20 (TXP_SATA)
SCK: R9.2, U1.V1 (SCK)
SCK#: R10.2, U1.V2 (SCK#)
SCS0: U1.V3 (SCS0), U2.L2 (#CS), U3.L2 (#CS)
SD0-CLK: SD/MMC.5 (CLK/SCLK), U1.L20 (SDC0_CLK/UART0_TX/PF2)
SD0-CMD: R42.1, SD/MMC.3 (CMD/DI), U1.L19 (SDC0_CMD/JTAG_DO1/PF3)
SD0-D0: RM3.2.2 (2), SD/MMC.7 (DAT0/DO), U1.M19 (SDC0_D0/JTAG_DI1/PF1)
SD0-D1: RM3.3.2 (2), SD/MMC.8 (DAT1/RES), U1.M20 (SDC0_D1/JTAG_MS1/PF0)
SD0-D2: RM3.1.2 (2), SD/MMC.1 (DAT2/RES), U1.K19 (SDC0_D2/JTAG_CK1/PF5)
SD0-D3: R41.1, SD/MMC.2 (CD/DAT3/CS), U1.K20 (SDC0_D3/UART0_RX/PF4)
SD0-DET#: RM3.4.2 (2), SD/MMC.9 (CP_E), U1.B6 (LCD1_D1/ATAA1/UART3_RX/EINT1/CSI1_D1/PH1)
SDQM0: U1.AC6 (SDQM0), U2.E7 (DML)
SDQM1: U1.W1 (SDQM1), U2.D3 (DMU)
SDQM2: U1.R2 (SDQM2), U3.E7 (DML)
SDQM3: U1.G1 (SDQM3), U3.D3 (DMU)
SDQS0: U1.AB6 (SDQS0), U2.F3 (DQSL)
SDQS0_N: U1.AC5 (SDQS0#), U2.G3 (#DQSL)
SDQS1: U1.AB1 (SDQS1), U2.C7 (DQSU)
SDQS1_N: U1.AA2 (SDQS1#), U2.B7 (#DQSU)
SDQS2: U1.R1 (SDQS2), U3.F3 (DQSL)
SDQS2_N: U1.P2 (SDQS2#), U3.G3 (#DQSL)
SDQS3: U1.K1 (SDQS3), U3.C7 (DQSU)
SDQS3_N: U1.J2 (SDQS3#), U3.B7 (#DQSU)
SD_VCC: C122.2, C124.2, L5.2, SD/MMC.4 (VDD)
SRST: R11.2, U1.AA6 (SRST)
TPX1: C139.2, U1.Y22 (XP_TP)
TPX2: C140.2, U1.AA22 (XN_TP)
TPY1: C141.2, U1.Y23 (YP_TP)
TPY2: C142.2, U1.AA23 (YN_TP)
TWI0-SCK: R79.1, U1.A15 (TWI0_SCK/PB0), U13.2 (SCK)
TWI0-SDA: R81.1, U1.B15 (TWI0_SDA/PB1), U13.1 (SDA)
UART0-RX: D2.A, R64.1, U1.B7 (UART0_RX/IR1_RX/PB23)
UART0-TX: U1.A7 (UART0_TX/IR1_TX/PB22), UART0.1
UBOOT_SEL: RECOVERY.2_1 (0), U1.W8 (UBOOT_SEL)
UDM0: U1.N20 (DM0), USB_OTG.D-
UDM1: U1.P20 (DM1), USB_HOST1.2
UDM2: U1.R20 (DM2), USB_HOST2.2
UDP0: U1.N21 (DP0), USB_OTG.D+
UDP1: U1.P21 (DP1), USB_HOST1.3
UDP2: U1.R21 (DP2), USB_HOST2.3
USB0-IDDET: R55.2, U1.B5 (LCD1_D4/ATAD0/UART4_TX/EINT4/CSI1_D4/PH4), USB_OTG.ID
USB0-VBUSDET: C135.1, R51.1, R54.2, U1.C5 (LCD1_D5/ATAD1/UART4_RX/EINT5/CSI1_D5/PH5)
USB1-DRV: R58.2, U1.A4 (LCD1_D6/ATAD2/UART5_TX/MS_BS/EINT6/CSI1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), U11.4 (EN)
USB2-DRV: R62.2, U1.A5 (LCD1_D3/ATAIRQ/UART3_CTS/EINT3/CSI1_D3/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), U12.4 (EN)
V+: 1.5V.1, C1.1, C2.1, C3.2, C4.2, C5.2, C6.2, C7.2, C8.2, C9.2, C10.2, C11.2, C12.2, C19.2, C20.2, C21.2, C22.2, C23.2, C24.2, C25.2, C26.2, C27.2, C28.2, C29.2, C30.2, C31.2, C32.2, C33.2, C34.2, C35.2, C36.2, C47.2, C48.2, C49.2, C50.2, C51.2, C52.2, C53.2, C54.2, C55.2, C56.2, C57.2, C58.2, C59.2, C60.2, C61.2, C62.2, C63.2, C64.2, C201.1, C203.1, C204.1, L14.2, R1.2, R2.2, R6.2, R86.1, U1.G5 (VCC_DRAM), U1.H5 (VCC_DRAM), U1.L5 (VCC_DRAM), U1.M5 (VCC_DRAM), U1.R5 (VCC_DRAM), U1.T5 (VCC_DRAM), U1.W5 (VCC_DRAM), U1.W6 (VCC_DRAM), U1.W7 (VCC_DRAM), U1.Y6 (VCC_DRAM), U2.A1 (VDDQ), U2.A8 (VDDQ), U2.B2 (VDD), U2.C1 (VDDQ), U2.C9 (VDDQ), U2.D2 (VDDQ), U2.D9 (VDD), U2.E9 (VDDQ), U2.F1 (VDDQ), U2.G7 (VDD), U2.H2 (VDDQ), U2.H9 (VDDQ), U2.K2 (VDD), U2.K8 (VDD), U2.N1 (VDD), U2.N9 (VDD), U2.R1 (VDD), U2.R9 (VDD), U3.A1 (VDDQ), U3.A8 (VDDQ), U3.B2 (VDD), U3.C1 (VDDQ), U3.C9 (VDDQ), U3.D2 (VDDQ), U3.D9 (VDD), U3.E9 (VDDQ), U3.F1 (VDDQ), U3.G7 (VDD), U3.H2 (VDDQ), U3.H9 (VDDQ), U3.K2 (VDD), U3.K8 (VDD), U3.N1 (VDD), U3.N9 (VDD), U3.R1 (VDD), U3.R9 (VDD)
VCC: 3.3V.1, C74.2, C75.2, C76.2, C92.2, C93.2, C94.2, C95.2, C96.2, C97.2, C98.2, C99.2, C100.2, C113.2, C114.2, C120.2, C121.2, C130.2, C131.2, C132.2, C143.2, C144.2, C164.1, C165.2, C191.1, C194.1, C195.2, C196.1, C198.2, C211.1, C212.1, C213.1, D1.A, L1.1, L2.1, L3.1, L5.1, L16.2, R20.1, R21.2, R22.1, R23.1, R24.2, R29.1, R30.2, R37.2, R39.1, R40.2, R41.2, R42.2, R55.1, R64.2, R79.2, R81.2, R91.1, R93.2, R94.2, R95.2, R96.2, RM1.1.2 (2), RM1.2.2 (2), RM1.3.2 (2), RM3.1.1 (1), RM3.2.1 (1), RM3.3.1 (1), RM3.4.1 (1), RM4.1.2 (2), RM4.2.2 (2), RM4.4.2 (2), U1.AB19 (HPVCCIN), U1.H8 (VCC), U1.H9 (VCC), U1.H10 (VCC), U1.H15 (VCC), U1.H19 (VCC_NAND), U1.J8 (VCC), U1.J9 (VCC), U1.J10 (VCC), U1.J14 (VCC), U1.J19 (VCC_NAND), U1.L15 (UVCC_T), U1.L16 (UVCC_C), U1.N19 (VCC_CARD), U1.P16 (PLLVP25), U1.T13 (VP_HDMI), U1.W12 (VCC_LVDS), U1.W13 (VCC_LVDS), U1.W14 (VCC_LVDS), U1.W15 (VCC33_TVOUT), U1.W16 (VCC33_TVIN), U4.12 (VCC), U4.37 (VCC), U6.8 (VCC), VR1.1 (VIN), VR1.3 (CE)
VCC/2: 1.2V_CPU.1, C65.2, C66.2, C67.2, C68.2, C69.2, C70.2, C166.1, C167.1, L12.2, U1.H11 (VDD_CPU), U1.H12 (VDD_CPU), U1.H13 (VDD_CPU), U1.H14 (VDD_CPU), U1.J12 (VDD_CPU), U1.J13 (VDD_CPU), U13.10 (DCDC2)
VCCINT: 1.2V_INT.1, C15.2, C16.2, C17.2, C18.2, C37.2, C38.2, C39.2, C40.2, C41.2, C42.2, C43.2, C44.2, C45.2, C46.2, C145.2, C148.2, C172.1, C173.1, C181.2, C184.2, L13.2, U1.J15 (VDD_INT), U1.J16 (VDD_INT), U1.K9 (VDD_INT), U1.K10 (VDD_INT), U1.K15 (VDD_INT), U1.K16 (ULVDD), U1.L8 (VDD_INT), U1.L9 (VDD_INT), U1.M8 (VDD_DLL), U1.M15 (VDD12_SATA), U1.M16 (VDD12_SATA), U1.N9 (VDD_DLL), U1.P9 (VDD_DLL), U1.R9 (VDD_INT), U1.R10 (VDD_INT), U1.T8 (VDD_INT), U13.17 (DCDC3)
VDD: 2.5V.1, C177.2, C178.2, C189.1, C190.2, C192.1, C193.1, U1.N15 (VDD25_SATA), U1.N16 (VDD25_SATA), U1.W17 (VDD25_TVIN), VR1.5 (VOUT)
VDDREG1: C83.2, C84.2, C85.2, L3.2, U5.44 (VDDREG), U5.45 (VDDREG)
VDD_RTC: C118.2, C119.2, C179.1, U1.K8 (RTC_VDD), U13.28 (LDO1)
VINT: C176.2, U13.26 (VINT)
VPP: 3.0VA.1, C123.2, C183.1, R87.1, U1.T19 (AVCC), U13.12 (LDO2), U15.1 (EN)
WEN: U1.T3 (SWE), U2.L3 (#WE), U3.L3 (#WE)
XTALI: C116.2, Q3.2, U1.N23 (CLK24M_IN)
XTALO: C117.2, Q3.1, U1.N22 (CLK24M_OUT)

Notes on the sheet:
POWER SUPPLY CIRCUIT
LI-ION_BATTERY
1 x [4Gb DDR3 SDRAM (256Mx16)]
MicroSD
BUTTON
USB-OTG
USB-HOSTs
NAND Flash
32Gb (4096M x 8bit)
EEPROM
MAC Address
16 Kbit
(2048 x 8)
HDMI
SATA
LED
ADC
GIGABIT ETHERNET TRANSCEIVER

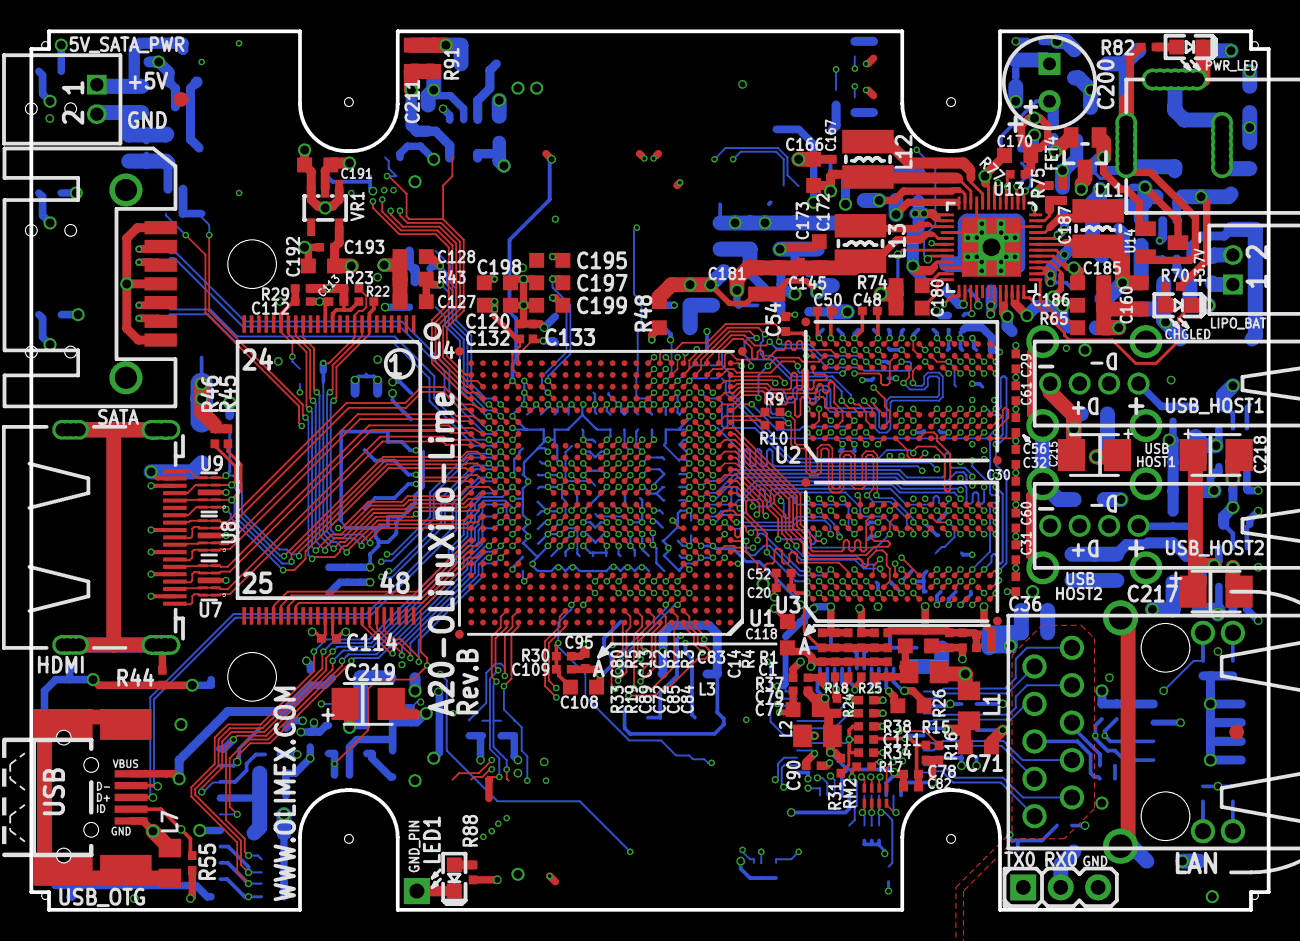
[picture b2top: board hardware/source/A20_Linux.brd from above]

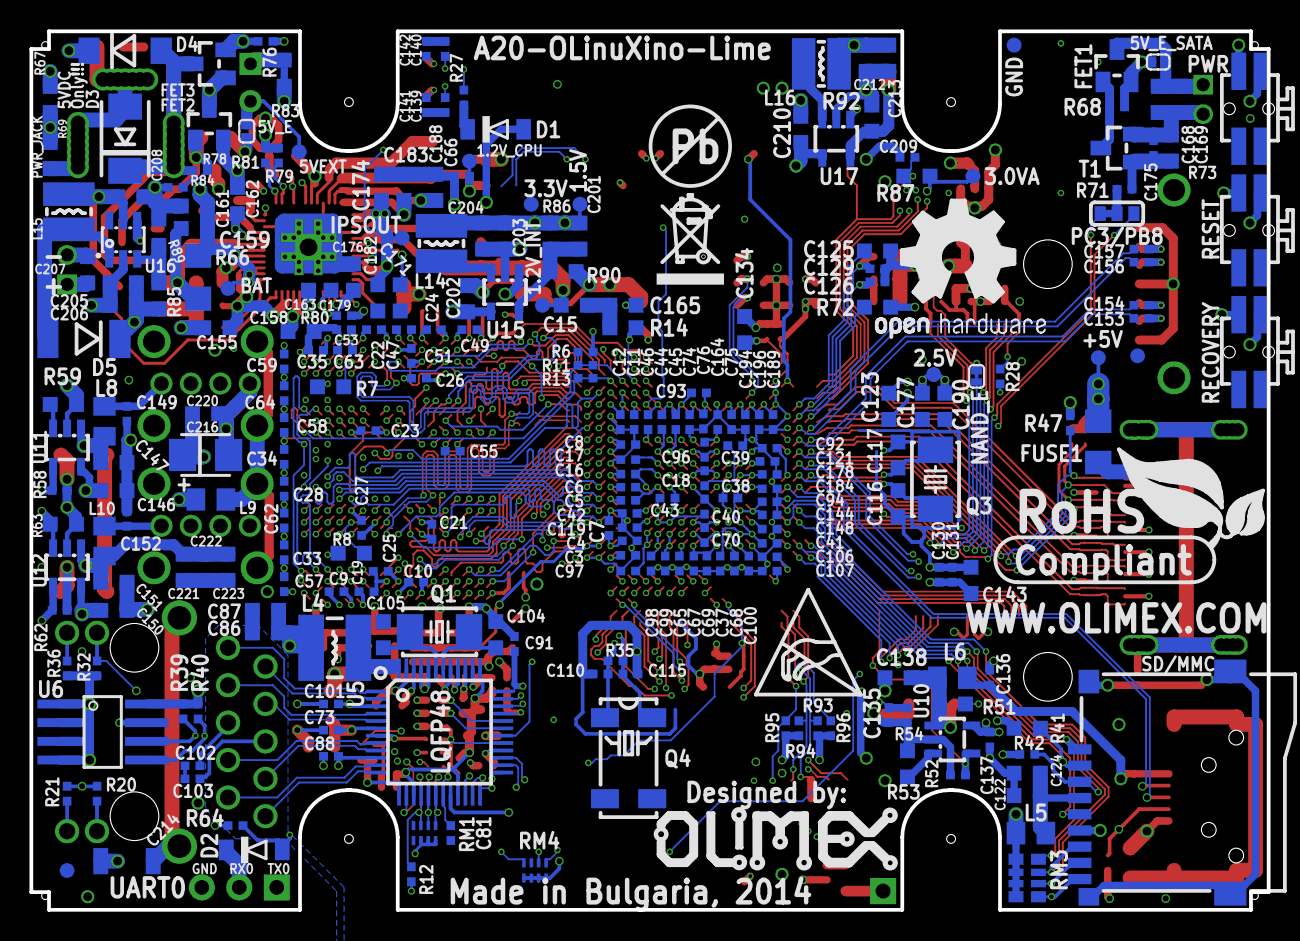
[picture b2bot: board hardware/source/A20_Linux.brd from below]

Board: 8 copper layers, 84.0 x 59.6 mm, 409 parts (268 on the bottom side), 285 nets.

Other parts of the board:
U$2: HAMMOND_1593LBK_A10_LIME
U$5: LOGO-OPENHARDWARE_8X8
U$6: OLIMEX1_V
U$9: PB
U$10: ESD_SYMBOL
U$11: RECYCLE_BIN1/8
U$12: ROHS

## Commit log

2015-02-06 Initial commit
    Added hardware files as well as the source files (Olimex A20-Lime)
2015-02-06 More Routing
    Added more DDR3 routing on the PCB
